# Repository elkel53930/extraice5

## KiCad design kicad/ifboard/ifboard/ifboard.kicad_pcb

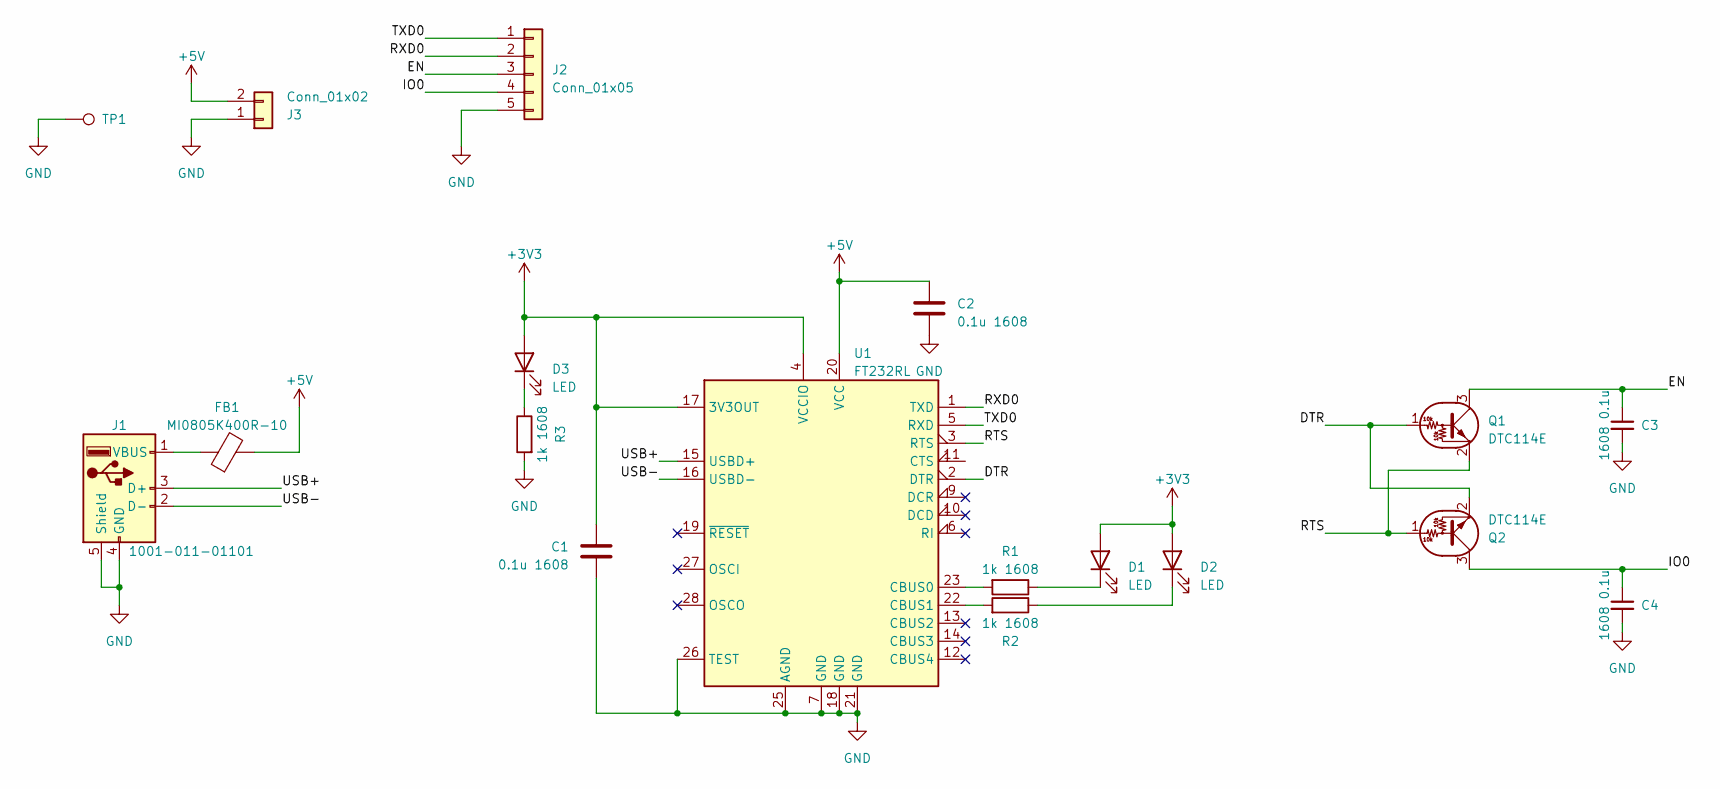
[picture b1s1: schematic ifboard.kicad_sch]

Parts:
C1, C2: 0.1u 1608; C_0603_1608Metric
C3, C4: 1608 0.1u; C_0603_1608Metric
D1, D2, D3: LED; LED_0603_1608Metric
FB1: MI0805K400R-10; C_0805_2012Metric
J1: 1001-011-01101; USB_A_CNCTech_1001-011-01101_Horizontal
J2: Conn_01x05; PinHeader_1x05_P2.00mm_Vertical
J3: Conn_01x02; PinHeader_1x02_P2.54mm_Vertical
Q1, Q2: DTC114E; SOT-723
R1, R2, R3: 1k 1608; R_0603_1608Metric
TP1: TestPoint_Loop_D2.50mm_Drill1.0mm
U1: FT232RL; SSOP-28_5.3x10.2mm_P0.65mm

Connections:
+3V3: C1.1, D1.2 (A), D2.2 (A), D3.2 (A), U1.4 (VCCIO), U1.17 (3V3OUT)
+5V: C2.1, FB1.2, J3.2, U1.20 (VCC)
/DTR: Q1.1 (B), Q2.2 (E), U1.2 (DTR)
/EN: C3.1, J2.3, Q1.3 (C)
/IO0: C4.1, J2.4, Q2.3 (C)
/RTS: Q1.2 (E), Q2.1 (B), U1.3 (RTS)
/RXD0: J2.2, U1.1 (TXD)
/TXD0: J2.1, U1.5 (RXD)
/USB+: J1.3 (D+), U1.15 (USBD+)
/USB-: J1.2 (D-), U1.16 (USBD-)
GND: C1.2, C2.2, C3.2, C4.2, J1.4 (GND), J1.5 (Shield), J2.5, J3.1, R3.2, TP1.1, U1.7 (GND), U1.18 (GND), U1.21 (GND), U1.25 (AGND), U1.26 (TEST)
unnamed: D1.1 (K), R1.1
unnamed: D2.1 (K), R2.1
unnamed: D3.1 (K), R3.1
unnamed: FB1.1, J1.1 (VBUS)
unnamed: R1.2, U1.23 (CBUS0)
unnamed: R2.2, U1.22 (CBUS1)

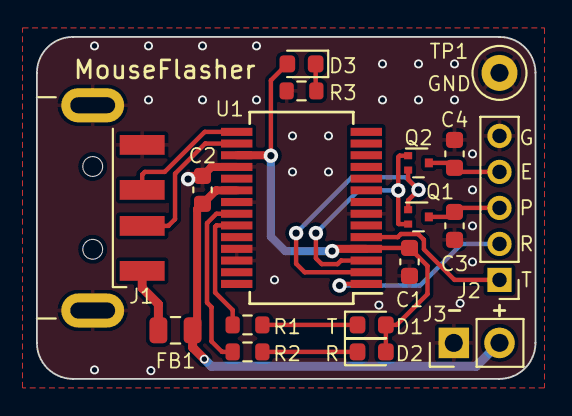
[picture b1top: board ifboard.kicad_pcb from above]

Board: 2 copper layers, 27.7 x 19.0 mm, 18 parts (0 on the bottom side), 17 nets.

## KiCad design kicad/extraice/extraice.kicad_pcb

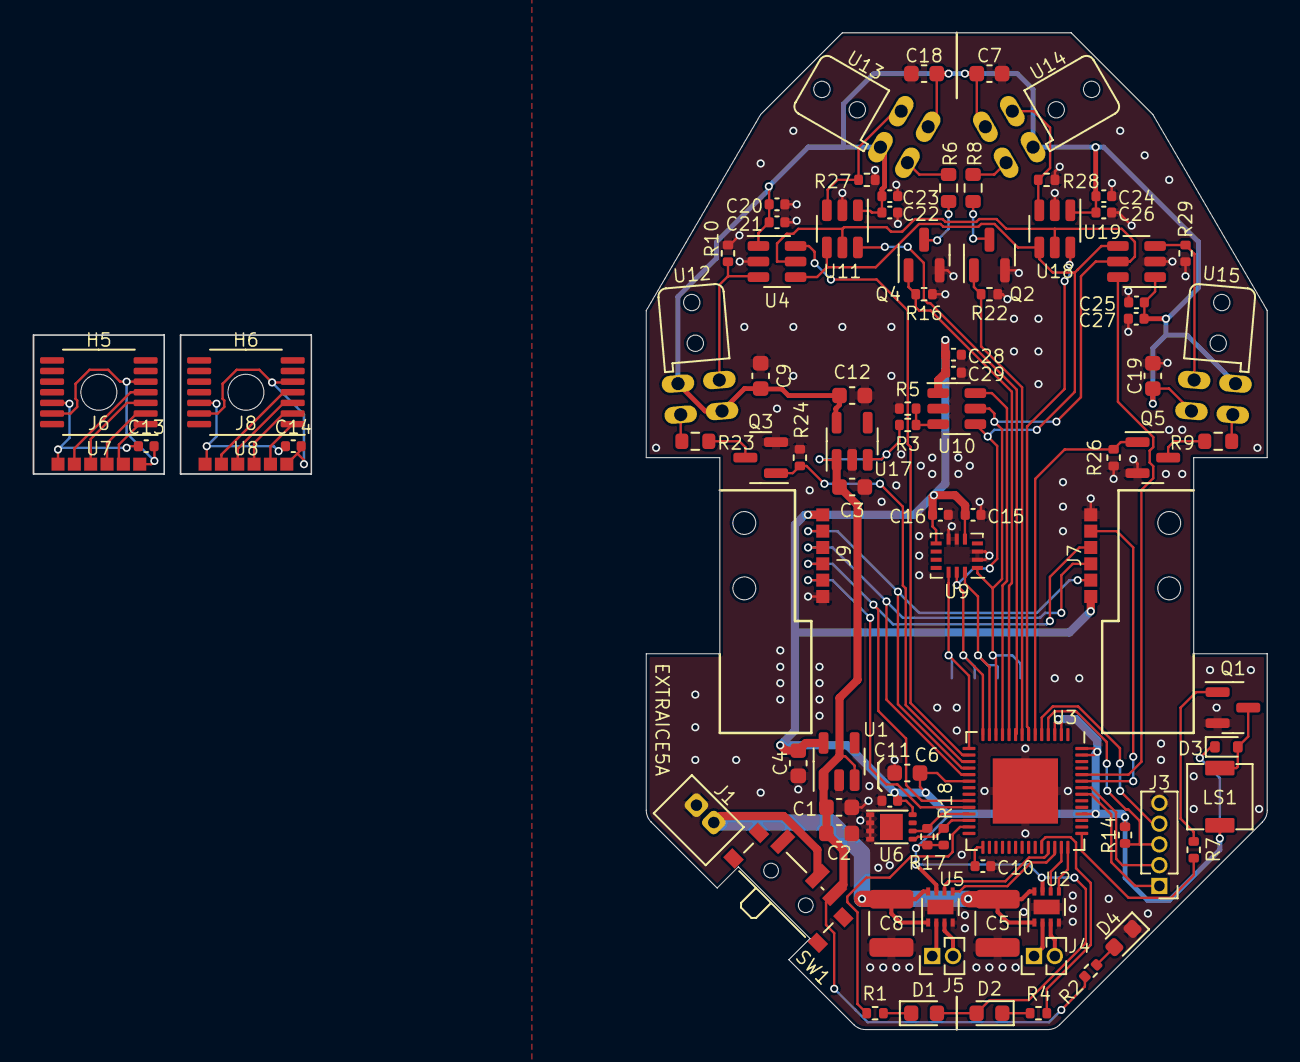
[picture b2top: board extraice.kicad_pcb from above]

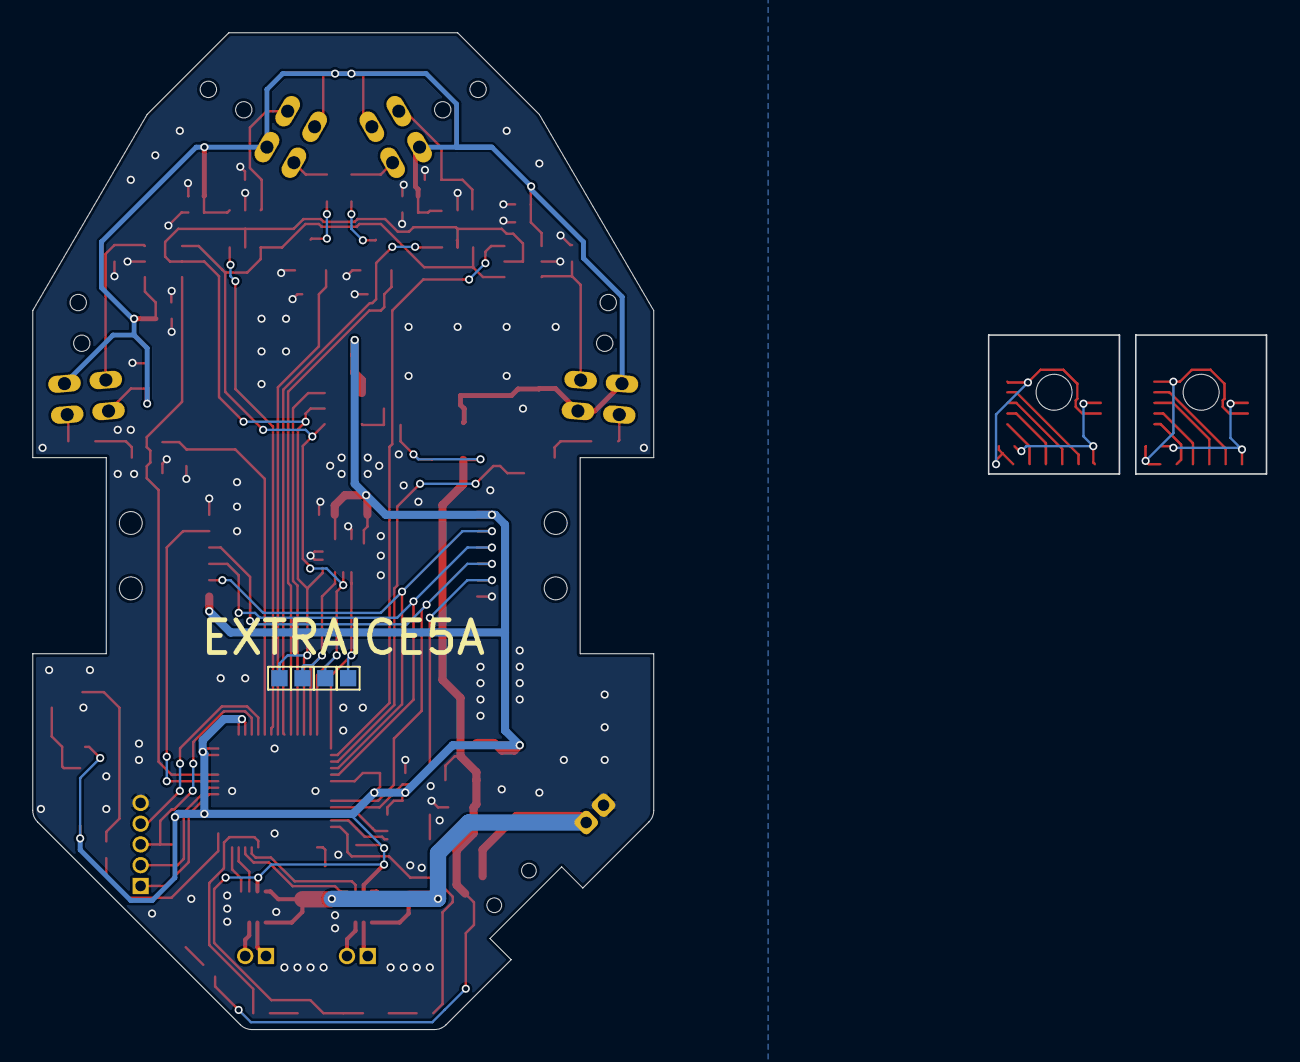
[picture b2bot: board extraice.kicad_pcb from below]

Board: 2 copper layers, 38.0 x 61.0 mm, 96 parts (4 on the bottom side), 71 nets.

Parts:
C1, C2, C3, C4, C6, C7, C9, C12, C18, C19: 1608 6.3V 10uF; C_0603_1608Metric
C5, C8: 3225 3.3u 16V; C_1210_3225Metric
C10, C11, C13, C14, C15, C16, C20, C22, C24, C25, C28: 1005 50V 0.1uF; C_0402_1005Metric
C21, C23, C26, C27, C29: 1005 25V 1uF; C_0402_1005Metric
D1, D2: 1608 LED; LED_0603_1608Metric
D3: BAS516; D_SOD-523
D4: 1608 R LED; LED_0603_1608Metric
H1, H2, H3, H4: Φ1.4; Hole1.4
H5, H6: Φ2.2; MountingHole_2.2mm_M2
J1: Conn_01x02; B2B-ZH
J3: Conn_01x05; PinHeader_1x05_P1.27mm_Vertical
J4, J5: Conn_01x02; PinHeader_1x02_P1.27mm_Vertical
J6, J8: EncSide; EncoderTerminal
J7, J9: MainSide; EncoderTerminal
LS1: SMT-0440-T-2-R
Q1: MMBT3904; SOT-23
Q2, Q3, Q4, Q5: IRLML6344; SOT-23
R1, R4, R17, R18: 1005 1k; R_0402_1005Metric
R2, R3, R5, R14, R16, R22, R24, R26: 1005 10k; R_0402_1005Metric
R6, R8, R9, R23: 1608 10; R_0603_1608Metric
R7: 1005 470 1%; R_0402_1005Metric
R10, R27, R28, R29: 1005 1k 0.5%; R_0402_1005Metric
SW1: PCM12SMTR; SW_SPDT_PCM12
TP1, TP2, TP3, TP4: TestPoint; TestPoint_Pad_1.0x1.0mm
U1, U17: XC6221B302GR; SOT-23-5
U2, U5: DRV8837C; WSON-8-1EP_2x2mm_P0.5mm_EP0.9x1.6mm
U3: ESP32-S3-PICO-1-N8R2; QFN-56-1EP_7x7mm_P0.4mm_EP4x4mm
U4, U10, U11, U18, U19: ADCS7476; SOT-23-6
U6: MB85RC64TA; LCC-8P-M04
U7, U8: AS5047D; TSSOP-14_4.4x5mm_P0.65mm
U9: LSM6DSR; Bosch_LGA-14_3x2.5mm_P0.5mm
U12, U13: PhotoSensorL
U14, U15: PhotoSensorR

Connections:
+3V0: C4.1, C6.2, C11.1, C15.1, C16.1, C28.1, C29.2, D1.2 (A), D2.2 (A), D3.1 (K), J7.1, J9.1, LS1.1, R14.2, R17.2, R18.2, U1.5 (VOUT), U2.7 (~SLEEP), U3.2 (VDD3P3), U3.3 (VDD3P3), U3.20 (VDD3P3_RTC), U3.46 (VDD3P3_CPU), U3.55 (VDDA), U3.56 (VDDA), U5.7 (~SLEEP), U6.8 (VDD), U9.5 (Vdd_IO), U9.8 (Vdd), U10.1 (VDD)
+BATT: C1.2, C2.2, C3.2, R2.2, R3.2, SW1.3 (C), U1.1 (VIN), U1.3 (CE), U17.1 (VIN), U17.3 (CE)
/BUZZ: R7.1, U3.43 (GPIO38)
/CHIP_PU: J3.3, R14.1, U3.4 (CHIP_PU)
/CS_BATT: U3.11 (GPIO6), U10.6 (~CS)
/CS_ENC_L: J9.5, U3.24 (GPIO18)
/CS_ENC_R: J7.5, U3.51 (GPIO45)
/CS_IMU: TP4.1, U3.15 (GPIO10), U9.12 (CS)
/CS_LF: U3.16 (GPIO11), U4.6 (~CS)
/CS_LS: U3.9 (GPIO4), U11.6 (~CS)
/CS_RF: U3.52 (GPIO46), U19.6 (~CS)
/CS_RS: U3.7 (GPIO2), U18.6 (~CS)
/CWCCW_L: U3.40 (GPIO35), U5.5 (IN2)
/CWCCW_R: U2.5 (IN2), U3.42 (GPIO37)
/GPIO0: J3.4, U3.5 (GPIO0)
/LED_0: R1.2, U3.27 (GPIO21)
/LED_1: R4.2, U3.38 (GPIO33)
/LED_POW: C7.2, C9.2, C12.1, C18.2, C19.2, C20.1, C21.2, C22.1, C23.2, C24.1, C25.1, C26.2, C27.2, U4.1 (VDD), U11.1 (VDD), U12.2, U12.3, U13.2, U13.3, U14.2, U14.3, U15.2, U15.3, U17.5 (VOUT), U18.1 (VDD), U19.1 (VDD)
/LF_EN: Q3.1 (G), R24.2, U3.17 (GPIO12)
/LS_EN: Q4.1 (G), R16.2, U3.10 (GPIO5)
/PWM_L: U3.39 (GPIO34), U5.6 (IN1)
/PWM_R: U2.6 (IN1), U3.41 (GPIO36)
/RF_EN: Q5.1 (G), R26.2, U3.6 (GPIO1)
/RS_EN: Q2.1 (G), R22.2, U3.8 (GPIO3)
/RXD: J3.2, U3.50 (U0RXD)
/SCL1: R17.1, U3.25 (GPIO19), U6.6 (SCL)
/SDA1: R18.1, U3.26 (GPIO20), U6.5 (SDA)
/SPI1_MISO: J7.3, J9.3, U3.19 (GPIO14)
/SPI1_MOSI: J7.2, J9.2, U3.18 (GPIO13)
/SPI1_SCK: J7.4, J9.4, U3.23 (GPIO17)
/SPI2_MISO: TP1.1, U3.12 (GPIO7), U4.5 (SDATA), U9.1 (SDO/SA0), U10.5 (SDATA), U11.5 (SDATA), U18.5 (SDATA), U19.5 (SDATA)
/SPI2_MOSI: TP2.1, U3.13 (GPIO8), U9.14 (SDA)
/SPI2_SCK: TP3.1, U3.14 (GPIO9), U4.4 (SCLK), U9.13 (SCL), U10.4 (SCLK), U11.4 (SCLK), U18.4 (SCLK), U19.4 (SCLK)
/TXD: J3.1, U3.49 (U0TXD)
/V_MOT: C5.1, C8.1, J1.2, SW1.2 (B), U2.1 (VM), U2.8 (VCC), U5.1 (VM), U5.8 (VCC)
GND: C1.1, C2.1, C3.1, C4.2, C5.2, C6.1, C7.1, C8.2, C9.1, C10.2, C11.2, C12.2, C15.2, C16.2, C18.1, C19.1, C20.2, C21.1, C22.2, C23.1, C24.2, C25.2, C26.1, C27.1, C28.2, C29.1, D4.1 (K), J1.1, J3.5, J7.6, J9.6, Q1.2 (E), Q2.2 (S), Q3.2 (S), Q4.2 (S), Q5.2 (S), R5.1, R10.2, R16.1, R22.1, R24.1, R26.1, R27.2, R28.2, R29.2, U1.2 (GND), U2.4 (GND), U2.9 (GND), U3.57 (GND), U4.2 (GND), U5.4 (GND), U5.9 (GND), U6.1 (A0), U6.2 (A1), U6.3 (A2), U6.4 (VSS), U9.2 (SDx), U9.3 (SCx), U9.6 (GND), U9.7 (GND), U10.2 (GND), U11.2 (GND), U17.2 (GND), U18.2 (GND), U19.2 (GND)
unnamed: D1.1 (K), R1.1
unnamed: D2.1 (K), R4.1
unnamed: D3.2 (A), LS1.2, Q1.3 (C)
unnamed: D4.2 (A), R2.1
unnamed: J4.1, U2.2 (OUT1)
unnamed: J4.2, U2.3 (OUT2)
unnamed: J5.1, U5.2 (OUT1)
unnamed: J5.2, U5.3 (OUT2)
unnamed: C13.1, J6.1, U7.12 (VDD3V3)
unnamed: J6.2, U7.4 (MOSI)
unnamed: J6.3, U7.3 (MISO)
unnamed: J6.4, U7.2 (CLK)
unnamed: J6.5, U7.1 (~CS)
unnamed: C13.2, J6.6, U7.5 (TST), U7.13 (GND)
unnamed: C14.1, J8.1, U8.12 (VDD3V3)
unnamed: J8.2, U8.4 (MOSI)
unnamed: J8.3, U8.3 (MISO)
unnamed: J8.4, U8.2 (CLK)
unnamed: J8.5, U8.1 (~CS)
unnamed: C14.2, J8.6, U8.5 (TST), U8.13 (GND)
unnamed: Q1.1 (B), R7.2
unnamed: Q2.3 (D), R8.1
unnamed: Q3.3 (D), R23.1
unnamed: Q4.3 (D), R6.1
unnamed: Q5.3 (D), R9.1
unnamed: R6.2, U13.4
unnamed: R8.2, U14.4
unnamed: R9.2, U15.4
unnamed: R23.2, U12.4
unnamed: C10.1, U3.29 (VDD_SPI)
unnamed: R10.1, U4.3 (VIN), U12.1
unnamed: R3.1, R5.2, U10.3 (VIN)
unnamed: R27.1, U11.3 (VIN), U13.1
unnamed: R28.1, U14.1, U18.3 (VIN)
unnamed: R29.1, U15.1, U19.3 (VIN)

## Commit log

2024-08-13 update schematics PDF
